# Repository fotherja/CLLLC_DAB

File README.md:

# CLLLC_DAB
CLLLC Dual active Bridge resonant converter v1

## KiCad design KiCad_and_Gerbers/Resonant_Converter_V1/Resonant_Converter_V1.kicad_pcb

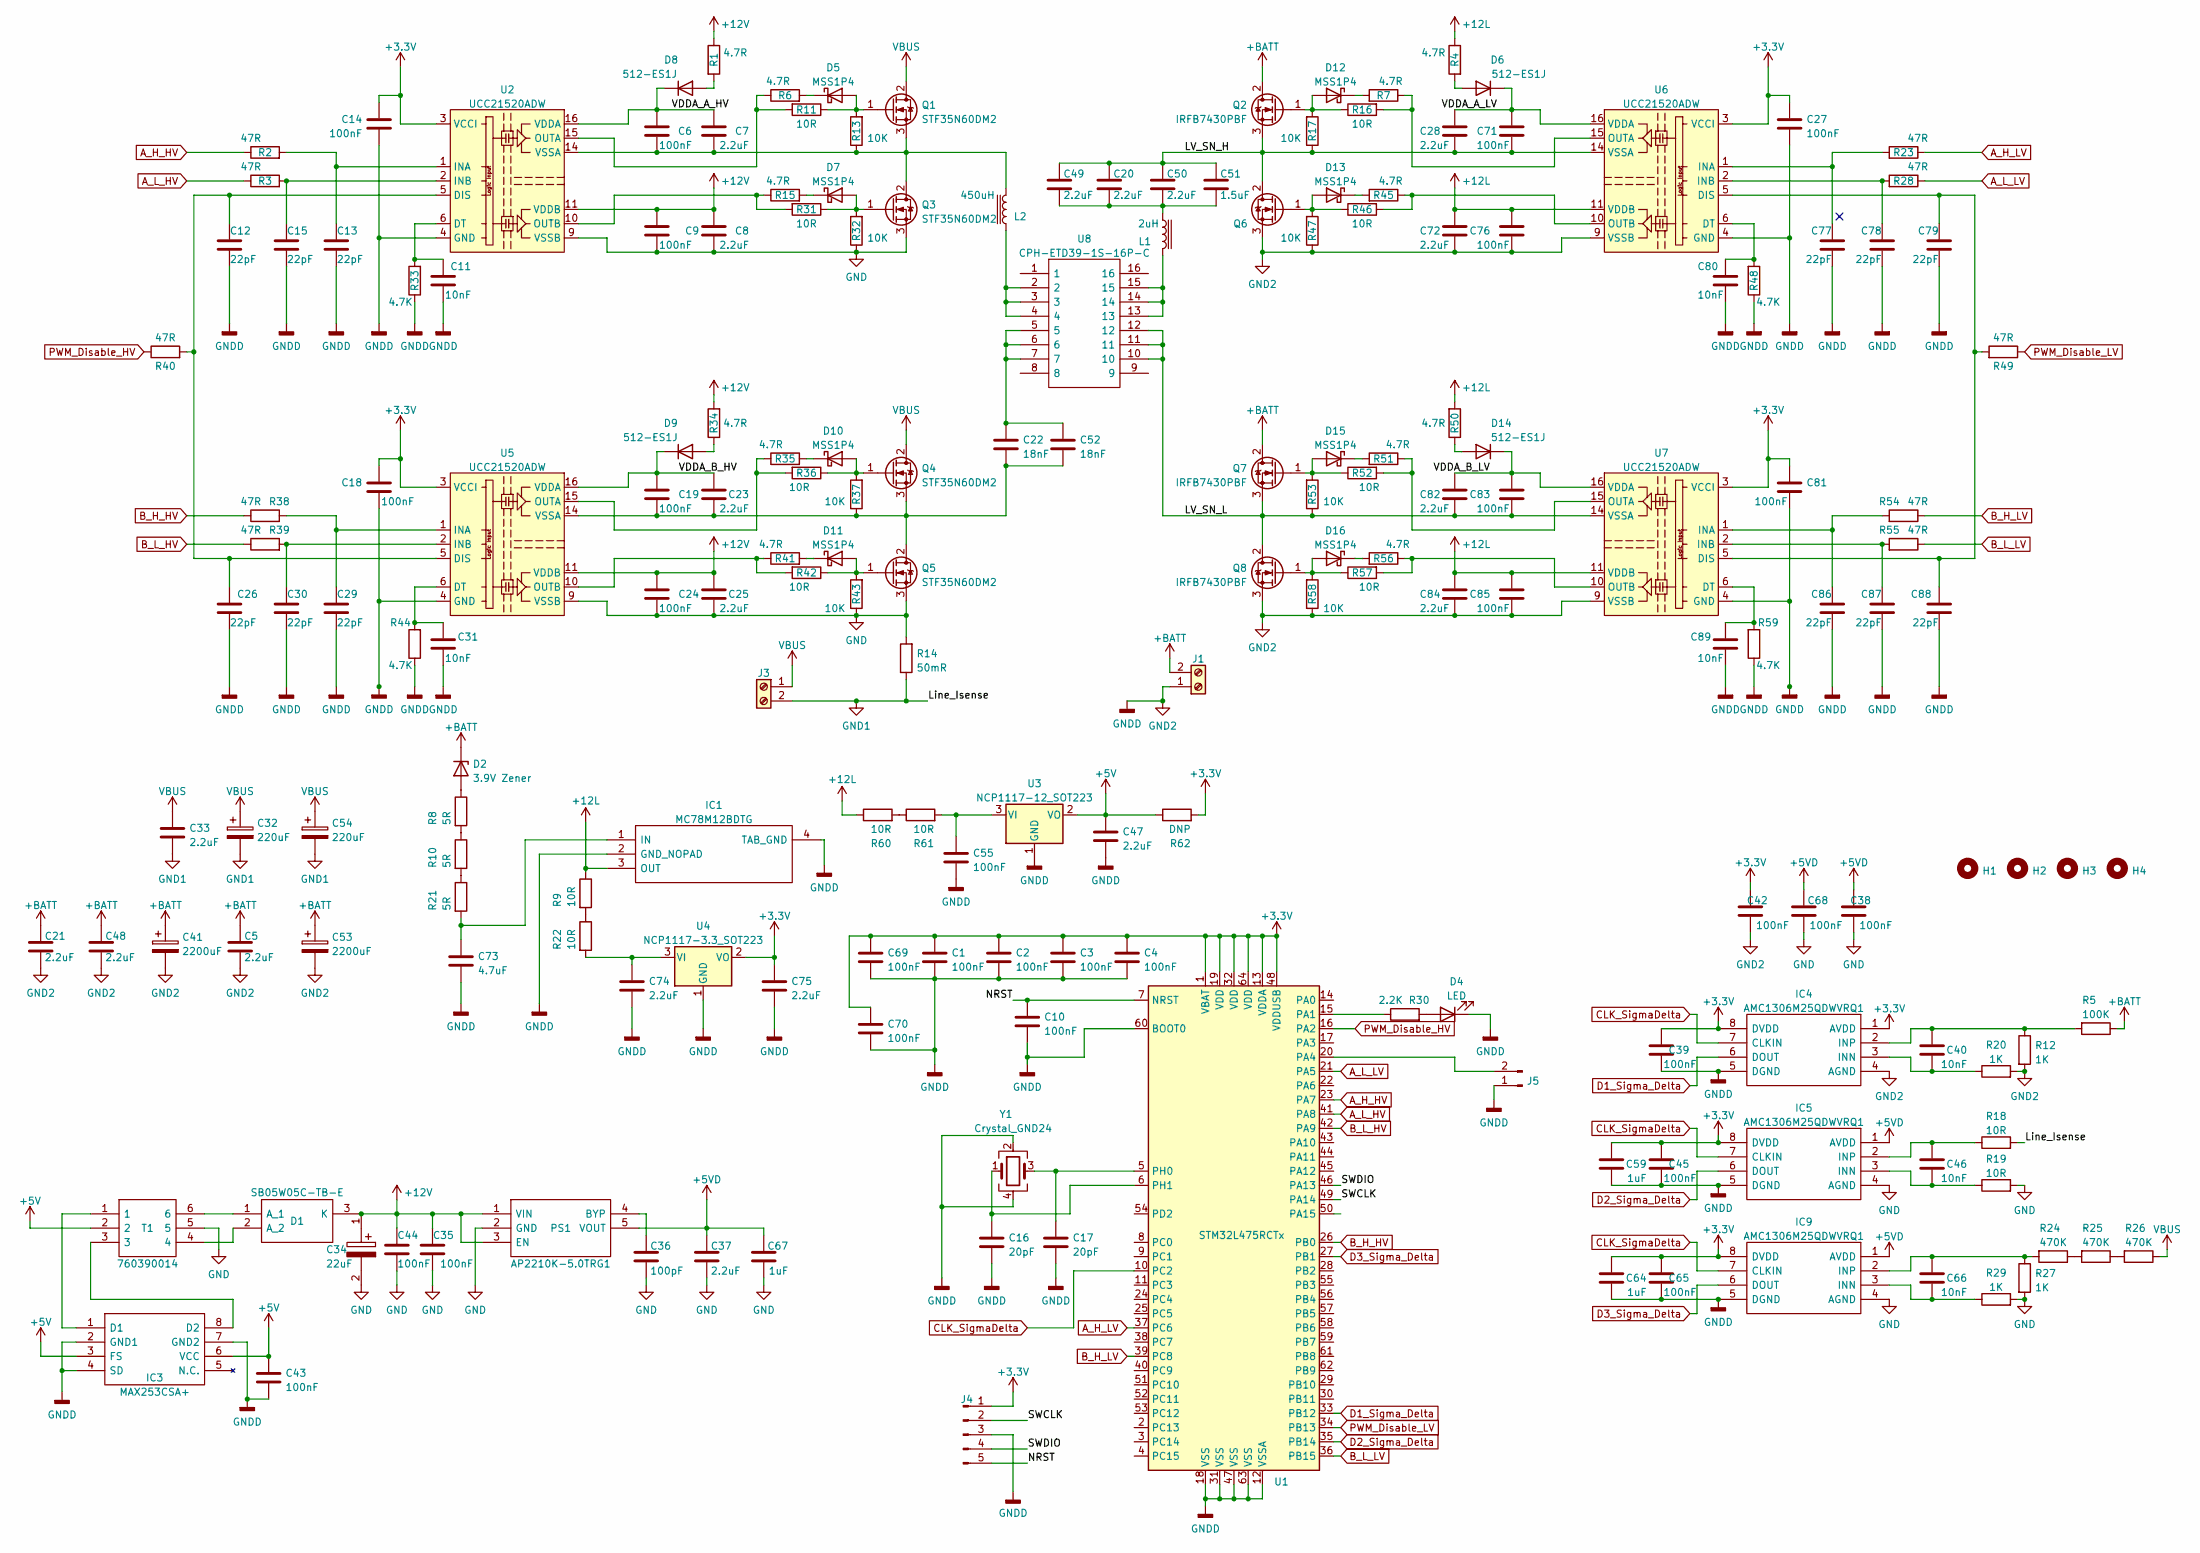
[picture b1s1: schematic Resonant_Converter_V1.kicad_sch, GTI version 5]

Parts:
C1, C2, C3, C4, C6, C9, C10, C14, C18, C19, C24, C27, C35, C38, C39, C42, C43, C44, C45, C55, C65, C68, C69, C70, C71, C76, C81, C83, C85: 100nF; C_0603_1608Metric
C5, C21, C48: 2.2uF; C_Rect_L13.0mm_W6.0mm_P10.00mm_FKS3_FKP3_MKS4
C7, C8, C23, C25, C28, C37, C47, C72, C74, C75, C82, C84: 2.2uF; C_0603_1608Metric
C11, C31, C40, C46, C66, C80, C89: 10nF; C_0603_1608Metric
C12, C13, C15, C26, C29, C30, C77, C78, C79, C86, C87, C88: 22pF; C_0603_1608Metric
C16, C17: 20pF; C_0603_1608Metric
C20, C49, C50: 2.2uF; C_Rect_L10.3mm_W7.2mm_P7.50mm_MKS4
C22, C52: 18nF; C_Rect_L13.0mm_W8.0mm_P10.00mm_FKS3_FKP3_MKS4
C32, C54: 220uF; CP_Radial_D25.0mm_P10.00mm_SnapIn
C33: 2.2uF; C_Rect_L13.0mm_W8.0mm_P10.00mm_FKS3_FKP3_MKS4
C34: 22uF; CAPPC3328X220N; Mouser Part Number 74-595D226X9020B2T
C36: 100pF; C_0603_1608Metric
C41, C53: 2200uF; CP_Radial_D18.0mm_P7.50mm
C51: 1.5uF; C_Rect_L10.3mm_W7.2mm_P7.50mm_MKS4
C59, C64, C67: 1uF; C_0603_1608Metric
C73: 4.7uF; C_0805_2012Metric
D1: SB05W05C-TB-E; SOT95P250X135-3N; Mouser Part Number 863-SB05W05C-TB-E
D2: 3.9V Zener; D_5W_P5.08mm_Vertical_AnodeUp
D4: LED; LED_0603_1608Metric
D5, D7, D10, D11, D12, D13, D15, D16: MSS1P4; D_MicroSMP
D6, D8, D9, D14: 512-ES1J; D_SMA
H1, H2, H3, H4: MountingHole; MountingHole_3.2mm_M3
IC1: MC78M12BDTG; TO229P990X238-4N; Mouser Part Number 863-MC78M12BDTG
IC3: MAX253CSA+; SOIC127P600X175-8N; Mouser Part Number 700-MAX253CSA
IC4, IC5, IC9: AMC1306M25QDWVRQ1; SOIC127P1150X280-8N; Mouser Part Number 595-MC1306M25QDWVRQ1
J1, J3: Screw_Terminal_01x02; TerminalBlock_bornier-2_P5.08mm
J4: Conn_01x05_Male; PinHeader_1x05_P1.27mm_Vertical
J5: Conn_01x02_Male; PinHeader_1x02_P1.27mm_Vertical
L1: 2uH; L_Toroid_Vertical_L28.6mm_W14.3mm_P11.43mm_Bourns_5700
L2: 450uH; L_Toroid_Vertical_L28.6mm_W14.3mm_P11.43mm_Bourns_5700
PS1: AP2210K-5.0TRG1; SOT95P282X130-5N; Mouser Part Number 621-AP2210K-5.0TRG1
Q1, Q3, Q4, Q5: STF35N60DM2; TO-220-3_Vertical
Q2, Q6, Q7, Q8: IRFB7430PBF; TO-220-3_Vertical
R1, R4, R6, R7, R15, R34, R35, R41, R45, R50, R51, R56: 4.7R; R_0603_1608Metric
R2, R3, R23, R28, R38, R39, R40, R49, R54, R55: 47R; R_0603_1608Metric
R5: 100K; R_0805_2012Metric
R8, R10, R21: 5R; R_0805_2012Metric
R9, R22, R60, R61: 10R; R_0805_2012Metric
R11, R16, R18, R19, R31, R36, R42, R46, R52, R57: 10R; R_0603_1608Metric
R12, R20, R27, R29: 1K; R_0603_1608Metric
R13, R17, R32, R37, R43, R47, R53, R58: 10K; R_0603_1608Metric
R14: 50mR; R_2512_6332Metric
R24, R25, R26: 470K; R_0805_2012Metric
R30: 2.2K; R_0603_1608Metric
R33, R44, R48, R59: 4.7K; R_0603_1608Metric
R62: DNP; R_0603_1608Metric
T1: 760390014; 760390015; Mouser Part Number 710-760390014
U1: STM32L475RCTx; LQFP-64_10x10mm_P0.5mm
U2, U5, U6, U7: UCC21520ADW; SOIC-16W_7.5x10.3mm_P1.27mm
U3: NCP1117-12_SOT223; SOT-223-3_TabPin2
U4: NCP1117-3.3_SOT223; SOT-223-3_TabPin2
U8: CPH-ETD39-1S-16P-C; ETD39-VER-16P; Manufacturer_Part_Number CPH-ETD39-1S-16P-C
Y1: Crystal_GND24; Crystal_SMD_Abracon_ABM10-4Pin_2.5x2.0mm

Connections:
+3.3V: C1.1, C2.1, C3.1, C4.1, C14.2, C18.2, C27.2, C39.1, C42.1, C45.1, C59.1, C64.1, C65.1, C69.1, C70.1, C75.1, C81.2, IC4.1 (AVDD), IC4.8 (DVDD), IC5.8 (DVDD), IC9.8 (DVDD), J4.1, R62.2, U1.1 (VBAT), U1.13 (VDDA), U1.19 (VDD), U1.32 (VDD), U1.48 (VDDUSB), U1.64 (VDD), U2.3 (VCCI), U2.8 (VCCI), U4.2 (VO), U5.3 (VCCI), U5.8 (VCCI), U6.3 (VCCI), U6.8 (VCCI), U7.3 (VCCI), U7.8 (VCCI)
+5V: C43.1, C47.1, IC3.3 (FS), IC3.6 (VCC), R62.1, T1.2, U3.2 (VO)
+5VD: C37.1, C38.1, C67.1, C68.1, IC5.1 (AVDD), IC9.1 (AVDD), PS1.5 (VOUT)
+12L: C72.1, C76.2, C84.1, C85.2, IC1.3 (OUT), R4.1, R9.1, R50.2, R60.1, U6.11 (VDDB), U7.11 (VDDB)
+12V: C8.1, C9.2, C24.2, C25.1, C34.1, C35.1, C44.1, D1.3 (K), PS1.1 (VIN), PS1.3 (EN), R1.1, R34.2, U2.11 (VDDB), U5.11 (VDDB)
+BATT: C5.1, C21.1, C41.1, C48.1, C53.1, D2.1 (K), J1.2, Q2.2 (D), Q7.2 (D), R5.1
/LV_SN_H: C20.1, C28.2, C49.1, C50.1, C51.1, C71.2, Q2.3 (S), Q6.2 (D), R17.1, U6.14 (VSSA)
/LV_SN_L: C82.2, C83.1, Q7.3 (S), Q8.2 (D), R53.1, U7.14 (VSSA), U8.10, U8.11, U8.12
/NRST: C10.1, J4.5, U1.7 (NRST)
/SWCLK: J4.2, U1.49 (PA14)
/SWDIO: J4.4, U1.46 (PA13)
/VDDA_A_HV: C6.1, C7.1, D8.1 (K), U2.16 (VDDA)
/VDDA_A_LV: C28.1, C71.1, D6.1 (K), U6.16 (VDDA)
/VDDA_B_HV: C19.2, C23.1, D9.1 (K), U5.16 (VDDA)
/VDDA_B_LV: C82.1, C83.2, D14.1 (K), U7.16 (VDDA)
A_H_HV: R2.1, U1.23 (PA7)
A_H_LV: R23.1, U1.37 (PC6)
A_L_HV: R3.1, U1.41 (PA8)
A_L_LV: R28.1, U1.21 (PA5)
B_H_HV: R38.1, U1.26 (PB0)
B_H_LV: R54.1, U1.39 (PC8)
B_L_HV: R39.1, U1.42 (PA9)
B_L_LV: R55.1, U1.36 (PB15)
CLK_SigmaDelta: IC4.7 (CLKIN), IC5.7 (CLKIN), IC9.7 (CLKIN), U1.10 (PC2)
D1_Sigma_Delta: IC4.6 (DOUT), U1.33 (PB12)
D2_Sigma_Delta: IC5.6 (DOUT), U1.35 (PB14)
D3_Sigma_Delta: U1.38 (PC7)
D4_Sigma_Delta: IC9.6 (DOUT), U1.27 (PB1)
GND: C8.2, C9.1, C24.1, C25.2, C34.2, C35.2, C36.2, C37.2, C38.2, C44.2, C67.2, C68.2, IC5.4 (AGND), IC9.4 (AGND), PS1.2 (GND), Q3.3 (S), Q5.3 (S), R14.2, R19.2, R27.2, R29.2, R32.1, R43.1, T1.5, U2.9 (VSSB), U5.9 (VSSB)
GND1: C32.2, C33.2, C54.2, J3.2, R14.1, R18.2
GND2: C1.2, C2.2, C3.2, C4.2, C5.2, C10.2, C11.1, C12.2, C13.2, C14.1, C15.2, C16.2, C17.2, C18.1, C21.2, C26.2, C27.1, C29.2, C30.2, C31.1, C39.2, C41.2, C42.2, C43.2, C45.2, C47.2, C48.2, C53.2, C55.2, C59.2, C64.2, C65.2, C69.2, C70.2, C72.2, C73.2, C74.2, C75.2, C76.1, C77.2, C78.2, C79.2, C80.1, C81.1, C84.2, C85.1, C86.2, C87.2, C88.2, C89.1, D4.1 (K), IC1.2 (GND_NOPAD), IC1.4 (TAB_GND), IC3.2 (GND1), IC3.4 (SD), IC3.7 (GND2), IC4.4 (AGND), IC4.5 (DGND), IC5.5 (DGND), IC9.5 (DGND), J1.1, J4.3, J5.1, Q6.3 (S), Q8.3 (S), R12.2, R20.2, R33.1, R44.1, R47.1, R48.1, R58.1, R59.1, U1.12 (VSSA), U1.18 (VSS), U1.31 (VSS), U1.47 (VSS), U1.60 (BOOT0), U1.63 (VSS), U2.4 (GND), U3.1 (GND), U4.1 (GND), U5.4 (GND), U6.4 (GND), U6.9 (VSSB), U7.4 (GND), U7.9 (VSSB), Y1.2, Y1.4
unnamed: C6.2, C7.2, L2.2, Q1.3 (S), Q3.2 (D), R13.1, U2.14 (VSSA)
unnamed: C11.2, R33.2, U2.6 (DT)
unnamed: C12.1, C26.1, R40.2, U2.5 (DIS), U5.5 (DIS)
unnamed: C13.1, R2.2, U2.1 (INA)
unnamed: C15.1, R3.2, U2.2 (INB)
unnamed: C16.1, U1.6 (PH1), Y1.1
unnamed: C17.1, U1.5 (PH0), Y1.3
unnamed: C19.1, C22.2, C23.2, C52.2, Q4.3 (S), Q5.2 (D), R37.1, U5.14 (VSSA)
unnamed: C20.2, C49.2, C50.2, C51.2, L1.2
unnamed: C22.1, C52.1, U8.5, U8.6, U8.7
unnamed: C29.1, R38.2, U5.1 (INA)
unnamed: C30.1, R39.2, U5.2 (INB)
unnamed: C31.2, R44.2, U5.6 (DT)
unnamed: C36.1, PS1.4 (BYP)
unnamed: C40.1, IC4.2 (INP), R5.2, R12.1
unnamed: C40.2, IC4.3 (INN), R20.1
unnamed: C46.1, IC5.2 (INP), R18.1
unnamed: C46.2, IC5.3 (INN), R19.1
unnamed: C66.1, IC9.2 (INP), R24.2, R27.1
unnamed: C66.2, IC9.3 (INN), R29.1
unnamed: C73.1, IC1.1 (IN), R21.2
unnamed: C74.1, R22.2, U4.3 (VI)
unnamed: C77.1, R23.2, U6.1 (INA)
unnamed: C78.1, R28.2, U6.2 (INB)
unnamed: C79.1, C88.1, R49.2, U6.5 (DIS), U7.5 (DIS)
unnamed: C80.2, R48.2, U6.6 (DT)
unnamed: C86.1, R54.2, U7.1 (INA)
unnamed: C87.1, R55.2, U7.2 (INB)
unnamed: C89.2, R59.2, U7.6 (DT)
unnamed: D1.1 (A_1), T1.6
unnamed: D1.2 (A_2), T1.4
unnamed: D2.2 (A), R8.1
unnamed: D4.2 (A), R30.2
unnamed: D5.1 (K), R6.2
unnamed: D5.2 (A), Q1.1 (G), R11.1, R13.2
unnamed: D6.2 (A), R4.2
unnamed: D7.1 (K), R15.2
unnamed: D7.2 (A), Q3.1 (G), R31.1, R32.2
unnamed: D8.2 (A), R1.2
unnamed: D9.2 (A), R34.1
unnamed: D10.1 (K), R35.2
unnamed: D10.2 (A), Q4.1 (G), R36.1, R37.2
unnamed: D11.1 (K), R41.2
unnamed: D11.2 (A), Q5.1 (G), R42.1, R43.2
unnamed: D12.1 (K), R7.2
unnamed: D12.2 (A), Q2.1 (G), R16.1, R17.2
unnamed: D13.1 (K), R45.2
unnamed: D13.2 (A), Q6.1 (G), R46.1, R47.2
unnamed: D14.2 (A), R50.1
unnamed: D15.1 (K), R51.2
unnamed: D15.2 (A), Q7.1 (G), R52.1, R53.2
unnamed: D16.1 (K), R56.2
unnamed: D16.2 (A), Q8.1 (G), R57.1, R58.2
unnamed: IC3.1 (D1), T1.1
unnamed: IC3.8 (D2), T1.3
unnamed: J5.2, U1.20 (PA4)
unnamed: L1.1, U8.13, U8.14, U8.15
unnamed: L2.1, U8.2, U8.3, U8.4
unnamed: R8.2, R10.1
unnamed: R10.2, R21.1
unnamed: R6.1, R11.2, U2.15 (OUTA)
unnamed: R15.1, R31.2, U2.10 (OUTB)
unnamed: R7.1, R16.2, U6.15 (OUTA)
unnamed: R9.2, R22.1
unnamed: R24.1, R25.2
unnamed: R25.1, R26.2
unnamed: R30.1, U1.15 (PA1)
unnamed: R35.1, R36.2, U5.15 (OUTA)
unnamed: R41.1, R42.2, U5.10 (OUTB)
unnamed: R45.1, R46.2, U6.10 (OUTB)
unnamed: R51.1, R52.2, U7.15 (OUTA)
unnamed: R56.1, R57.2, U7.10 (OUTB)
unnamed: R60.2, R61.1
unnamed: C55.1, R61.2, U3.3 (VI)
PWM_Disable_HV: R40.1, U1.16 (PA2)
PWM_Disable_LV: R49.1, U1.34 (PB13)
VBUS: C32.1, C33.1, C54.1, J3.1, Q1.2 (D), Q4.2 (D), R26.1

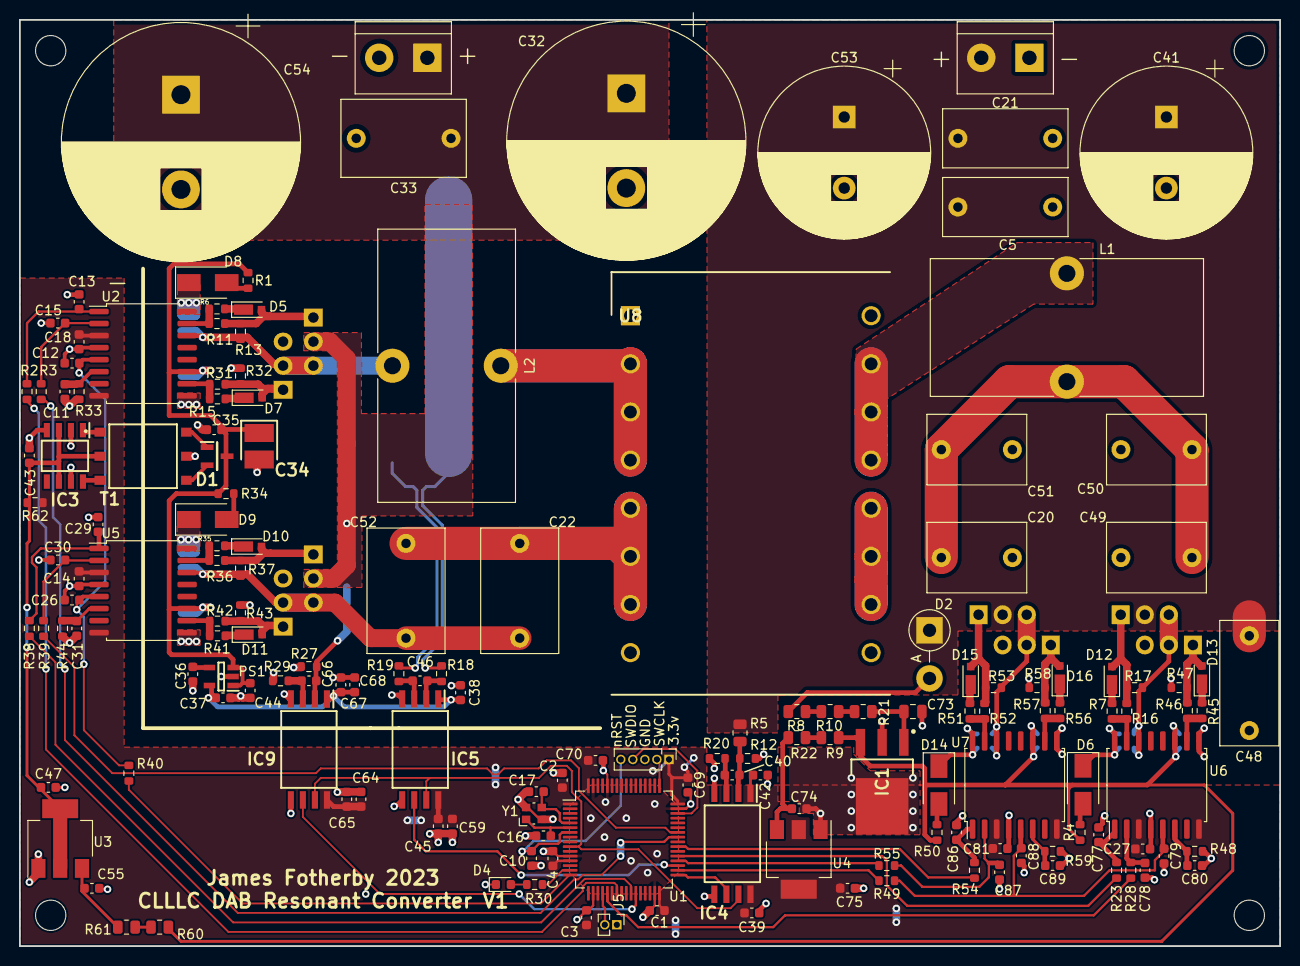
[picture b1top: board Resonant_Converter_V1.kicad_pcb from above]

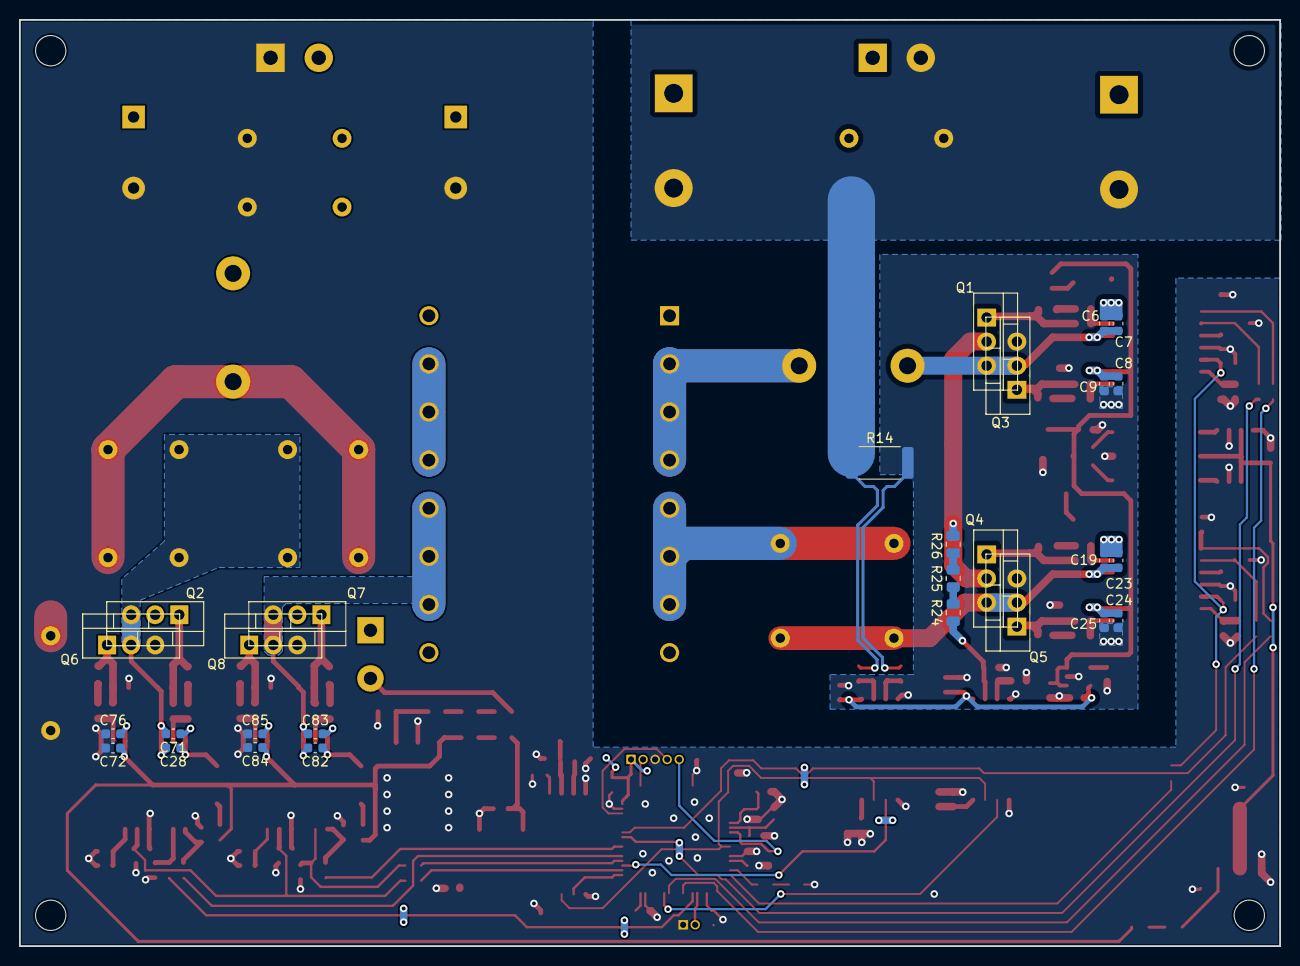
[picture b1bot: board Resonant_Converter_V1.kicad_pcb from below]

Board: 2 copper layers, 133.0 x 97.8 mm, 193 parts (28 on the bottom side), 107 nets.

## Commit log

2023-07-16 KiCad upload
    KiCad and gerbers uploaded for v1 PCB
2023-07-22 Small mods to schematic
